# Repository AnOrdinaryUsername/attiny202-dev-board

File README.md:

# ATtiny202 Dev Board

A small development board for the ATtiny202 microcontroller and my first PCB!

## Features

- Power-Only USB Type-C Receptacle
- 3.3V LDO Voltage Regulator
- Red Power On LED Indicator
- UPDI Interface

## Programming

Programmable using [SerialUPDI](https://github.com/SpenceKonde/AVR-Guidance/blob/master/UPDI/jtag2updi.md) (recommended)
or [jtag2updi](https://github.com/ElTangas/jtag2updi).

Install avrdude following these [instructions](https://github.com/avrdudes/avrdude/wiki/Building-AVRDUDE-for-Linux) on their GitHub. Don't install through your system's package manager, or you'll get an older version of avrdude that doesn't have SerialUPDI. 

Before you can use avr-gcc to build the program, you must first download the device-pack files
from [Microchip's Packs Repository](https://packs.download.microchip.com/). Download the one that
says `Microchip ATtiny Series Device Support (3.1.260)` and then unzip it to a directory of your
choice.

```
mkdir atpack
mv Microchip.ATtiny_DFP.3.1.260.atpack atpack
cd atpack && unzip Microchip.ATtiny_DFP.3.1.260.atpack
```

You can now build specific projects using the `Makefile`

```
make build proj=blinky atpack=~/atpack/
```

Or build all projects

```
make
```

After you've built your project and connected the USB to TTL adapter to your PC and the UPDI interface, 
upload the build files using avrdude.

```
avrdude -vvv -c serialupdi -b 230400 -P /dev/ttyUSB0 -p t202 -U flash:w:your_build_file.hex:a
```

Breaking it down (better explanation at [avrdude docs](https://avrdudes.github.io/avrdude/8.0/avrdude_4.html#Option-Descriptions)):
- `-vvv` Enables verbose output
- `-c` Specifies the programmer to be used
- `-b` Sets the baud rate
- `-P` Selects which port to use
- `-p` Says which microcontroller we're programming for (t202 stands for ATtiny202). You can view the list of parts supported at [D. List of Parts](https://avrdudes.github.io/avrdude/8.0/avrdude_45.html#List-of-Parts)
- `-U` Write the hex file to flash memory and auto-detect the file format (usually Intel Hex)

Alternatively, you can also use the `Makefile`:

```
make upload proj=blinky port=/dev/ttyUSB0
```

## Schematic

## Manufacturing/Assembly

JLCPCB formatted BOM, CPL, and Gerber files can be found in [hardware](/hardware).

Here's how the fully assembled PCB looks.

Top             |  Bottom
:-------------------------:|:-------------------------:
 |

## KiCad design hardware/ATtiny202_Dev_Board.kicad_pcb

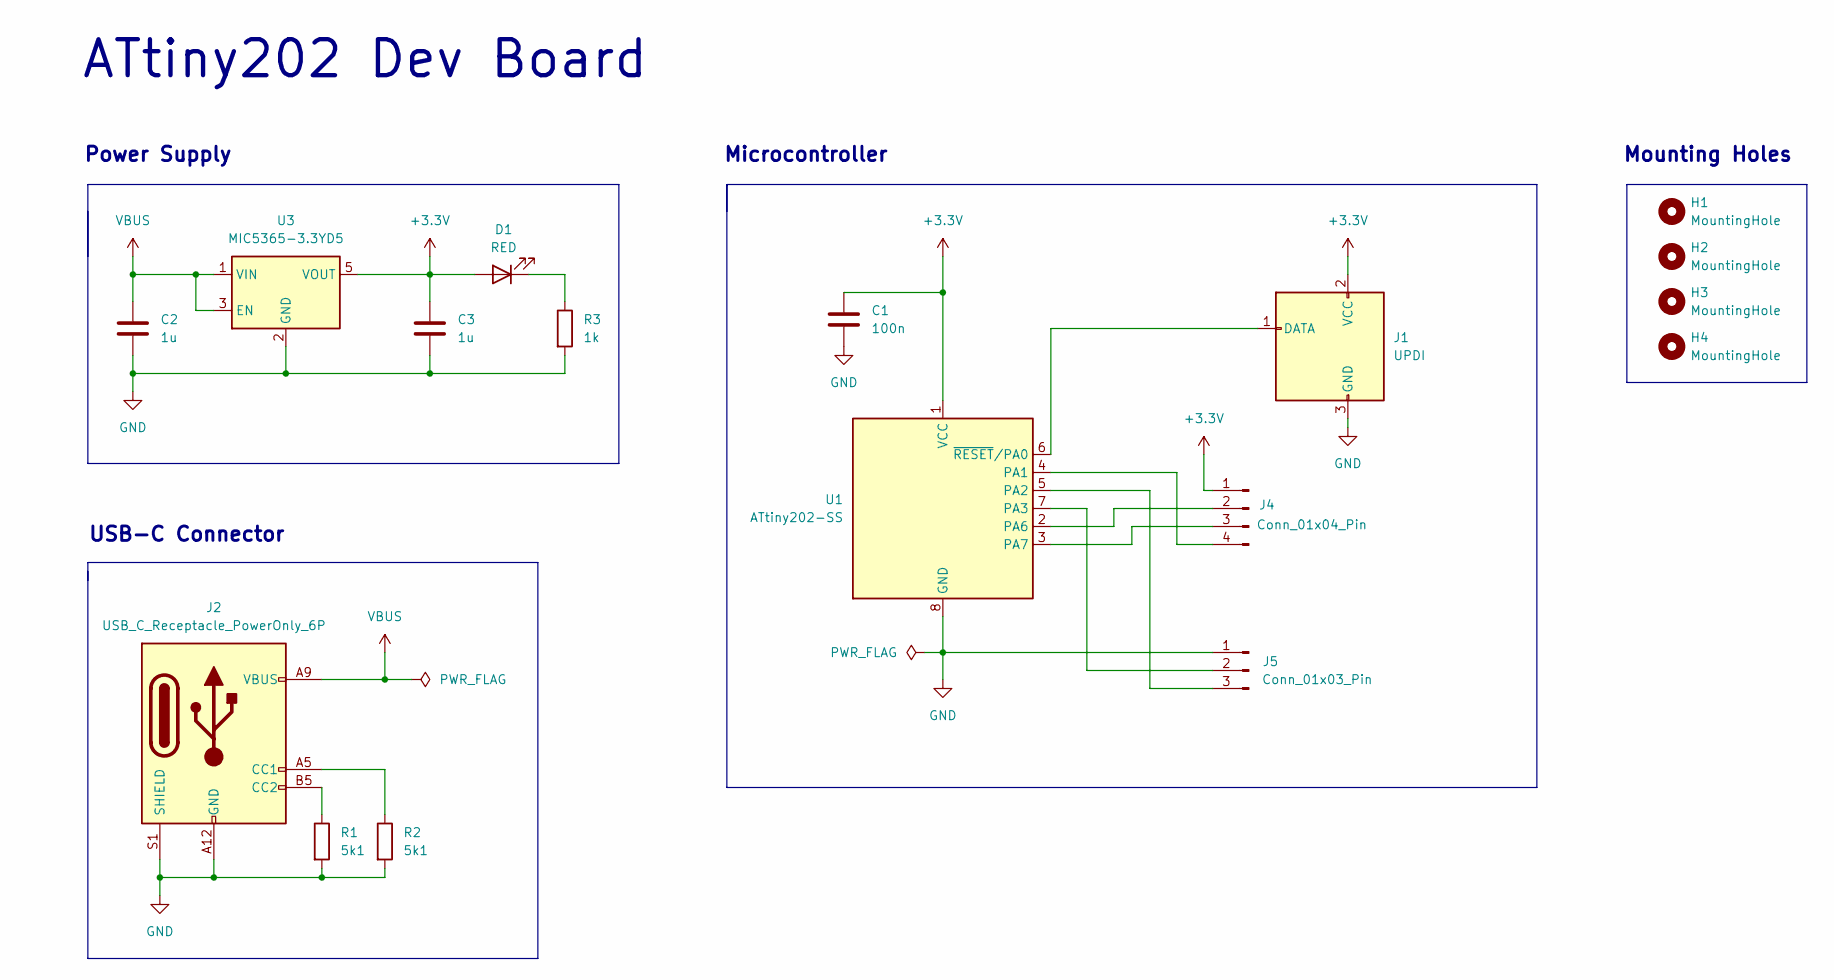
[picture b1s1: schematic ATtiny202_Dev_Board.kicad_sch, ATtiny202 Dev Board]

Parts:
C1: 100n; C_0402_1005Metric; JLCPCB Part # C387941
C2, C3: 1u; C_0402_1005Metric; JLCPCB Part # C76999
D1: RED; LED_0603_1608Metric; JLCPCB Part # C2286
H1, H2, H3, H4: MountingHole; MountingHole_2.2mm_M2
J1: UPDI; PinHeader_1x03_P2.54mm_Vertical; JLCPCB Part # C5360899
J2: USB_C_Receptacle_PowerOnly_6P; USB_C_Receptacle_GCT_USB4125-xx-x_6P_TopMnt_Horizontal; JLCPCB Part # C456012
J4: Conn_01x04_Pin; PinHeader_1x04_P2.54mm_Vertical; JLCPCB Part # C5116483
J5: Conn_01x03_Pin; PinHeader_1x03_P2.54mm_Vertical; JLCPCB Part # C5360899
R1, R2: 5k1; R_0402_1005Metric; JLCPCB Part # C138073
R3: 1k; R_0402_1005Metric; JLCPCB Part # C106235
U1: ATtiny202-SS; SOIC-8_3.9x4.9mm_P1.27mm; JLCPCB Part # C616039
U3: MIC5365-3.3YD5; SOT-23-5; JLCPCB Part # C626098

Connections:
+3.3V: C1.1, C3.1, D1.2 (A), J1.2 (VCC), J4.1, U1.1 (VCC), U3.5 (VOUT)
GND: C1.2, C2.2, C3.2, J1.3 (GND), J2.A12 (GND), J2.B12 (GND), J2.S1 (SHIELD), J5.1, R1.2, R2.2, R3.2, U1.8 (GND), U3.2 (GND)
unnamed: D1.1 (K), R3.1
unnamed: J1.1 (DATA), U1.6 (~RESET/PA0)
unnamed: J2.A5 (CC1), R2.1
unnamed: J2.B5 (CC2), R1.1
unnamed: J4.2, U1.2 (PA6)
unnamed: J4.3, U1.3 (PA7)
unnamed: J4.4, U1.4 (PA1)
unnamed: J5.2, U1.7 (PA3)
unnamed: J5.3, U1.5 (PA2)
VBUS: C2.1, J2.A9 (VBUS), J2.B9 (VBUS), U3.1 (VIN), U3.3 (EN)

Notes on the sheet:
Microcontroller
USB-C Connector
Power Supply
Mounting Holes
ATtiny202 Dev Board

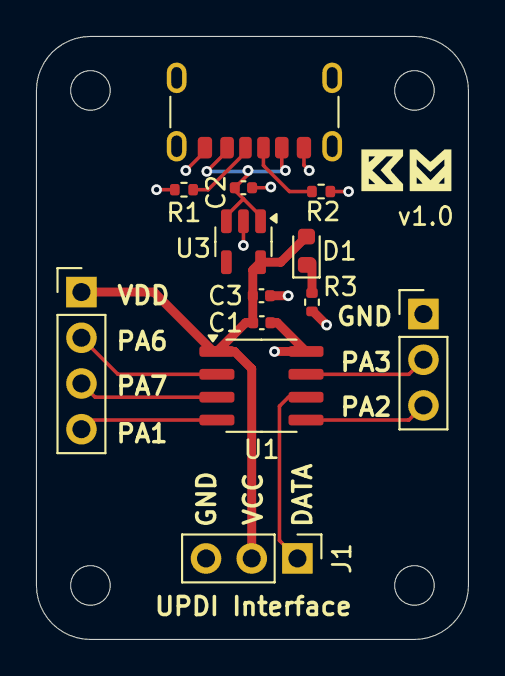
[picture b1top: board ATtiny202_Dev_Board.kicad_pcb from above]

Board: 2 copper layers, 24.0 x 33.5 mm, 17 parts (0 on the bottom side), 12 nets.

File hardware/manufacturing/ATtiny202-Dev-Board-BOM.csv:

"Comment","Designator","Qty","Footprint","JLCPCB Part #"
"100n","C1","1","Capacitor_SMD:C_0402_1005Metric","C387941"
"1u","C2,C3","2","Capacitor_SMD:C_0402_1005Metric","C76999"
"1k","R3","1","Resistor_SMD:R_0402_1005Metric","C106235"
"5k1","R1,R2","2","Resistor_SMD:R_0402_1005Metric","C138073"
"ATtiny202-SS","U1","1","Package_SO:SOIC-8_3.9x4.9mm_P1.27mm","C616039"
"Conn_01x03_Pin","J5","1","Connector_PinHeader_2.54mm:PinHeader_1x03_P2.54mm_Vertical","C5360899"
"Conn_01x04_Pin","J4","1","Connector_PinHeader_2.54mm:PinHeader_1x04_P2.54mm_Vertical","C5116483"
"MIC5365-3.3YD5","U3","1","Package_TO_SOT_SMD:SOT-23-5","C626098"
"RED","D1","1","LED_SMD:LED_0603_1608Metric","C2286"
"UPDI","J1","1","Connector_PinHeader_2.54mm:PinHeader_1x03_P2.54mm_Vertical","C5360899"
"USB_C_Receptacle_PowerOnly_6P","J2","1","Connector_USB:USB_C_Receptacle_GCT_USB4125-xx-x_6P_TopMnt_Horizontal","C456012"

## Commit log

2024-09-17 Add manufactured PCB images
2024-09-17 Add assembled PCB images
2024-09-19 Include USART example
2024-09-19 Add errata from datasheet
2024-10-01 Describe how to build projects using Makefile
2024-10-02 Fix fuses command
2024-10-02 Change USART example to use button as input
2024-10-02 Fix errors in Button schematic
    Previous schematic errors:
    - D2 was not a light-emitting diode
    - USB-C should be the 16p one not 14p
2024-10-04 Show actual memory usage of program build
    The size of the hex file doesn't represent size of the program
    in flash memory. Use "avr-objdump -P mem-usage" to get an
    accurate reading.
    Add way to generate assembler listings with associted C code
    and line numbers.
2024-10-11 Add ability to turn LED on/off w/ USART
    - Use LED to show how to transmit data from PC to MCU.
    - Move button code to ISR because it won't work in main
    loop otherwise.
    - Adjust schematic to show internal pull-up resistor usage
    and LED connection.
2024-10-17 Show TWI/I2C math
